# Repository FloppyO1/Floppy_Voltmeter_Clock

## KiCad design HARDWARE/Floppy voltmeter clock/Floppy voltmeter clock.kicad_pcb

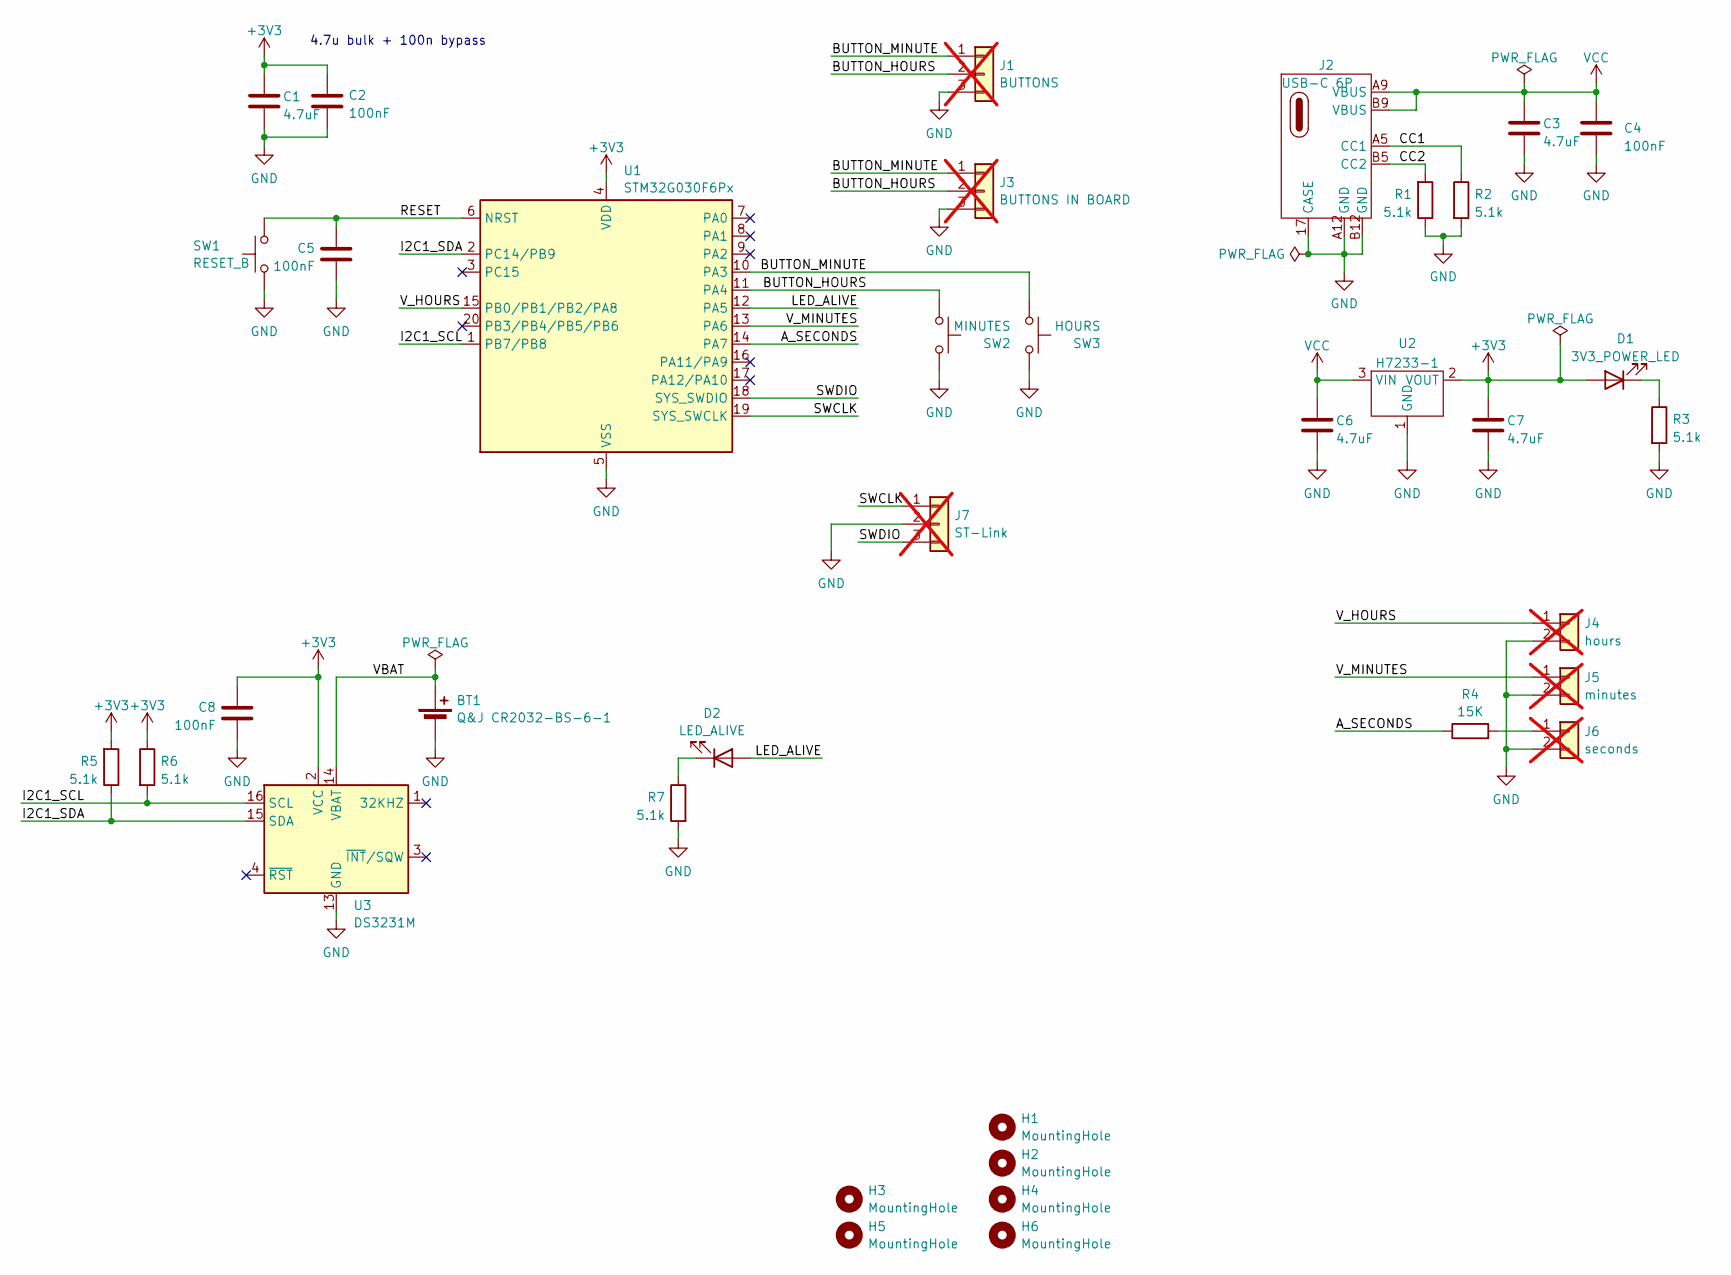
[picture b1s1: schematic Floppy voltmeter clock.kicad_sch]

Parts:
BT1: Q&J CR2032-BS-6-1; BatteryHolder_Keystone_1060_1x2032; LCSC C70377
C1, C3, C6, C7: 4.7uF; C_0805_2012Metric_Pad1.18x1.45mm_HandSolder; LCSC C967590
C2, C5, C8: 100nF; C_0805_2012Metric_Pad1.18x1.45mm_HandSolder; LCSC C476766
C4: 100nF; C_0805_2012Metric_Pad1.18x1.45mm_HandSolder; Voltage 50V; LCSC C476766
D1: 3V3_POWER_LED; LED_0805_2012Metric_Pad1.15x1.40mm_HandSolder; LCSC C7496834
D2: LED_ALIVE; LED_0805_2012Metric_Pad1.15x1.40mm_HandSolder; LCSC C965815
H1, H2, H3, H4, H5, H6: MountingHole; MountingHole_3.2mm_M3_Pad_Via
J1: BUTTONS; JST_XH_B3B-XH-A_1x03_P2.50mm_Vertical; LCSC C144394; not fitted
J2: USB-C 6P; USB-C (only power); LCSC C2927027
J3: BUTTONS IN BOARD; JST_XH_B3B-XH-A_1x03_P2.50mm_Vertical; LCSC C144394; not fitted
J4: hours; JST_XH_B2B-XH-A_1x02_P2.50mm_Vertical; LCSC C158012; not fitted
J5: minutes; JST_XH_B2B-XH-A_1x02_P2.50mm_Vertical; LCSC C158012; not fitted
J6: seconds; JST_XH_B2B-XH-A_1x02_P2.50mm_Vertical; LCSC C158012; not fitted
J7: ST-Link; PinHeader_1x03_P2.54mm_Vertical; not fitted
R1, R2, R3, R5, R6, R7: 5.1k; R_0805_2012Metric_Pad1.20x1.40mm_HandSolder; LCSC C23186
R4: 15K; R_0805_2012Metric_Pad1.20x1.40mm_HandSolder; LCSC C23186
SW1: RESET_B; SMD BUTTON 5.1x5.1; LCSC C318884
SW2: MINUTES; SMD BUTTON 5.1x5.1; LCSC C318884
SW3: HOURS; SMD BUTTON 5.1x5.1; LCSC C318884
U1: STM32G030F6Px; TSSOP-20_4.4x6.5mm_P0.65mm; LCSC C724040
U2: H7233-1; SOT-23; LCSC C277859
U3: DS3231M; SOIC-16W_7.5x10.3mm_P1.27mm; LCSC C9866

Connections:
+3V3: C1.1, C2.1, C7.1, C8.1, D1.2 (A), R5.2, R6.1, U1.4 (VDD), U2.2 (VOUT), U3.2 (VCC)
/A_SECONDS: R4.1, U1.14 (PA7)
/BUTTON_HOURS: J1.2, J3.2, SW2.1, U1.11 (PA4)
/BUTTON_MINUTE: J1.1, J3.1, SW3.1, U1.10 (PA3)
/CC1: J2.A5 (CC1), R2.1
/CC2: J2.B5 (CC2), R1.2
/I2C1_SCL: R6.2, U1.1 (PB7/PB8), U3.16 (SCL)
/I2C1_SDA: R5.1, U1.2 (PC14/PB9), U3.15 (SDA)
/LED_ALIVE: D2.2 (A), U1.12 (PA5)
/RESET: C5.1, SW1.2, U1.6 (NRST)
/SWCLK: J7.1, U1.19 (SYS_SWCLK)
/SWDIO: J7.3, U1.18 (SYS_SWDIO)
/VBAT: BT1.1 (+), U3.14 (VBAT)
/V_HOURS: J4.1, U1.15 (PB0/PB1/PB2/PA8)
/V_MINUTES: J5.1, U1.13 (PA6)
GND: BT1.2 (-), C1.2, C2.2, C3.2, C4.2, C5.2, C6.2, C7.2, C8.2, J1.3, J2.17 (CASE), J2.18 (CASE), J2.19 (CASE), J2.20 (CASE), J2.A12 (GND), J2.B12 (GND), J3.3, J4.2, J5.2, J6.2, J7.2, R1.1, R2.2, R3.2, R7.2, SW1.1, SW2.2, SW3.2, U1.5 (VSS), U2.1 (GND), U3.5 (GND), U3.6 (GND), U3.7 (GND), U3.8 (GND), U3.9 (GND), U3.10 (GND), U3.11 (GND), U3.12 (GND), U3.13 (GND)
unnamed: D1.1 (K), R3.1
unnamed: D2.1 (K), R7.1
unnamed: J6.1, R4.2
VCC: C3.1, C4.1, C6.1, J2.A9 (VBUS), J2.B9 (VBUS), U2.3 (VIN)

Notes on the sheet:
4.7u bulk + 100n bypass

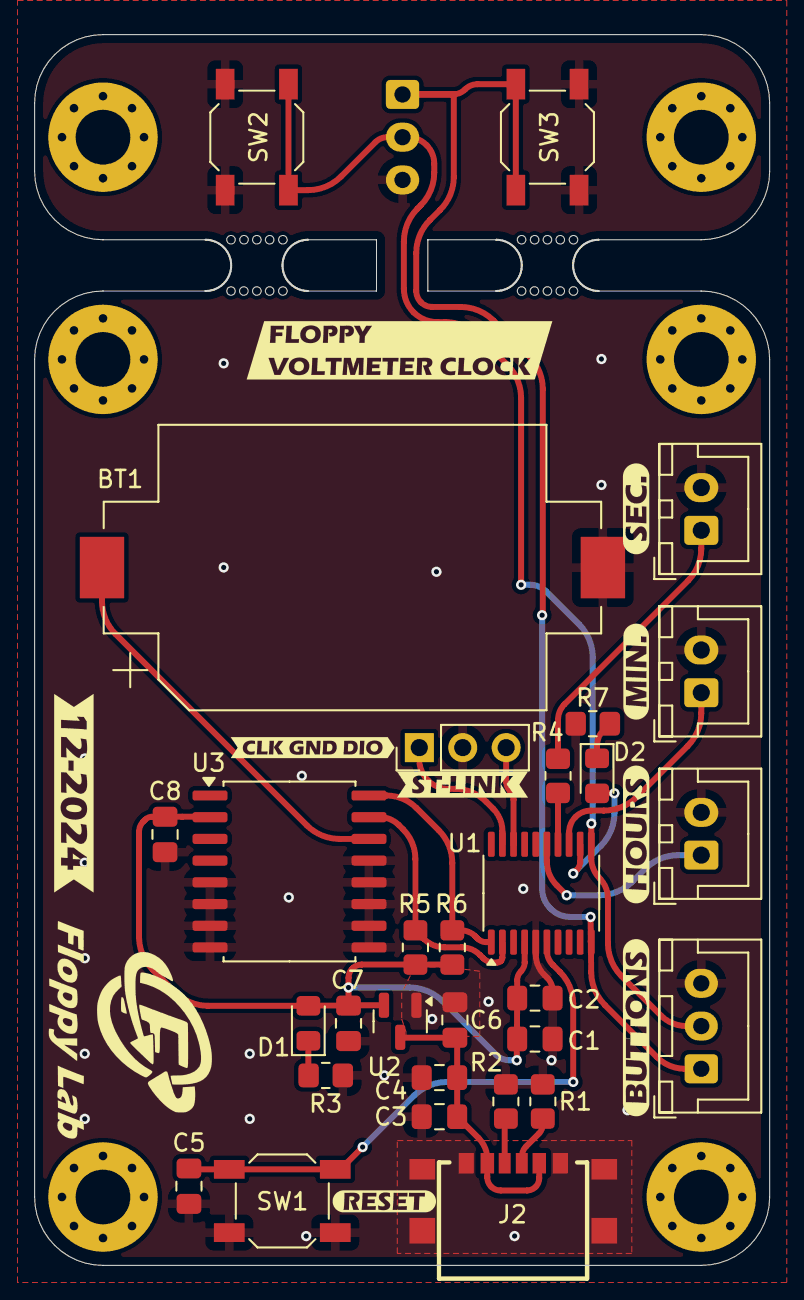
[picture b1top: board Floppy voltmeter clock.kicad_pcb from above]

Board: 2 copper layers, 42.9 x 71.9 mm, 48 parts (1 on the bottom side), 20 nets.

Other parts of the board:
kibuzzard-675B2D1E: G***; kibuzzard-675B2D1E
kibuzzard-675B2D2F: G***; kibuzzard-675B2D2F
kibuzzard-675B2D7A: G***; kibuzzard-675B2D7A
kibuzzard-675B2D7E: G***; kibuzzard-675B2D7E
kibuzzard-675B2D96: G***; kibuzzard-675B2D96
kibuzzard-675B2EC4: G***; kibuzzard-675B2EC4
kibuzzard-677D17B8: G***; kibuzzard-677D17B8
kibuzzard-6786B9A9: G***; kibuzzard-6786B9A9
kibuzzard-6786B82B: G***; kibuzzard-6786B82B
mouse-bite-3mm-slot, mouse-bite-3mm-slot#2: VAL**; mouse-bite-3mm-slot

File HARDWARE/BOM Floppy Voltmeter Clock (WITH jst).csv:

Reference;Value;LCSC;Footprint;Datasheet;Qty
BT1;Q&J CR2032-BS-6-1;C70377;Battery:BatteryHolder_Keystone_1060_1x2032;https://www.lcsc.com/datasheet/lcsc_datasheet_2409302302_Q-J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;1
C1-C3-C6-C7;4.7uF;C967590;Capacitor_SMD:C_0805_2012Metric_Pad1.18x1.45mm_HandSolder;~;4
C2-C4-C5-C8;100nF;C476766;Capacitor_SMD:C_0805_2012Metric_Pad1.18x1.45mm_HandSolder;~;4
D1;3V3_POWER_LED;C7496834;LED_SMD:LED_0805_2012Metric_Pad1.15x1.40mm_HandSolder;~;1
D2;LED_ALIVE;C965815;LED_SMD:LED_0805_2012Metric_Pad1.15x1.40mm_HandSolder;~;1
J1;BUTTONS;C144394;Connector_JST:JST_XH_B3B-XH-A_1x03_P2.50mm_Vertical;~;1
J2;USB-C 6P;C2927027;_MIA footprint:USB-C (only power);https://datasheet.lcsc.com/lcsc/2201121330_DEALON-USB-TYPE-C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;1
J3;BUTTONS IN BOARD;C144394;Connector_JST:JST_XH_B3B-XH-A_1x03_P2.50mm_Vertical;~;1
J4;hours;C158012;Connector_JST:JST_XH_B2B-XH-A_1x02_P2.50mm_Vertical;~;1
J5;minutes;C158012;Connector_JST:JST_XH_B2B-XH-A_1x02_P2.50mm_Vertical;~;1
J6;seconds;C158012;Connector_JST:JST_XH_B2B-XH-A_1x02_P2.50mm_Vertical;~;1
R1-R2-R3-R5-R6-R7;5.1k;C23186;Resistor_SMD:R_0805_2012Metric_Pad1.20x1.40mm_HandSolder;~;6
R4;15K;C23186;Resistor_SMD:R_0805_2012Metric_Pad1.20x1.40mm_HandSolder;~;1
SW1;RESET_B;C318884;_MIA footprint:SMD BUTTON 5.1x5.1;~;1
SW2;MINUTES;C318884;_MIA footprint:SMD BUTTON 5.1x5.1;~;1
SW3;HOURS;C318884;_MIA footprint:SMD BUTTON 5.1x5.1;~;1
U1;STM32G030F6Px;C724040;Package_SO:TSSOP-20_4.4x6.5mm_P0.65mm;https://www.st.com/resource/en/datasheet/stm32g030f6.pdf;1
U2;H7233-1;C277859;Package_TO_SOT_SMD:SOT-23;https://datasheet.lcsc.com/lcsc/2304140030_Shanghai-Siproin-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;1
U3;DS3231M;C9866;Package_SO:SOIC-16W_7.5x10.3mm_P1.27mm;http://datasheets.maximintegrated.com/en/ds/DS3231.pdf;1

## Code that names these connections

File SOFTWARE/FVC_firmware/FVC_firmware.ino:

/*
  This code was written by Floppy Lab for the Floppy Voltmeter Clock
  This code is under license (check it on the github folder)
  https://github.com/FloppyO1/Floppy_Voltmeter_Clock
*/

#include <Wire.h>
#include <DS3231.h>

// FLOPPY BOARD 3.1
#define V_ORE PB0
#define V_MINUTE PA6
#define A_SECOND PA7
#define SDA PB9
#define SCL PB8
#define BUTTON_HOURS PA4
#define BUTTON_MINUTES PA3


DS3231 myRTC;
bool h12Flag;
bool pmFlag;

void setup() {
  pinMode(V_ORE, OUTPUT);
  pinMode(V_MINUTE, OUTPUT);
  pinMode(A_SECOND, OUTPUT);
  pinMode(BUTTON_MINUTES, INPUT_PULLUP);
  pinMode(BUTTON_HOURS, INPUT_PULLUP);

  Serial.begin(9600);
  Wire.setSDA(SDA);
  Wire.setSCL(SCL);
  Wire.begin();
  delay(500);
  analogWriteResolution(8);

  myRTC.setClockMode(true);  // set to 12h
}

uint32_t timeDebouce = 0;

void loop() {
  setHourHand(myRTC.getHour(h12Flag, pmFlag));
  setMinuteHand(myRTC.getMinute());
  setSecondsHand(myRTC.getSecond());

  if (digitalRead(BUTTON_HOURS) == LOW) {
    if (millis() - timeDebouce >= 300) {
      uint8_t hour = myRTC.getHour(h12Flag, pmFlag);
      if (hour + 1 > 12) {
        hour = 1;
      } else {
        hour++;
      }
      myRTC.setHour(hour);
      timeDebouce = millis();
    }
  }
  if (digitalRead(BUTTON_MINUTES) == LOW) {
    if (millis() - timeDebouce >= 300) {
      uint8_t min = myRTC.getMinute();
      if (min + 1 > 60) {
        min = 1;
      } else {
        min++;
      }
      myRTC.setMinute(min);
      timeDebouce = millis();
    }
  }
}

void setHourHand(int n) {
  if (!n) n = 0;
  float x = 256 / 12;  // 12 number of position (12 hours)
  x = x * (n-1);
  int duty = x;
  analogWrite(V_ORE, duty);
}
void setMinuteHand(int n) {
  if (!n) n = 0;
  float x = 256 / 60;  // 60 number of position (60 minutes)
  x = x * n;
  int duty = x;
  analogWrite(V_MINUTE, duty);
}
void setSecondsHand(int n) {
  if (!n) n = 0;
  float x = 256 / 60;  // 60 number of position (60 seconds)
  x = x * n;
  int duty = x;
  analogWrite(A_SECOND, duty);
}

// void setNumber(int n, int nmax) {
//   if (!n) n = 0;
//   float x = 256 / nmax;
//   x = x * (n - 1);
//   int duty = x;
//   analogWrite(V_ORE, duty);
// }

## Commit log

2025-01-20 added voltmeter custom graphics ITA/ENG
2025-03-02 updated 3d design (centered the seconds ampmeter)
